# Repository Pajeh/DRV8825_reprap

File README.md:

# DRV8825_reprap
DRV8825 Stepper Schematic based on reprap from Pololu

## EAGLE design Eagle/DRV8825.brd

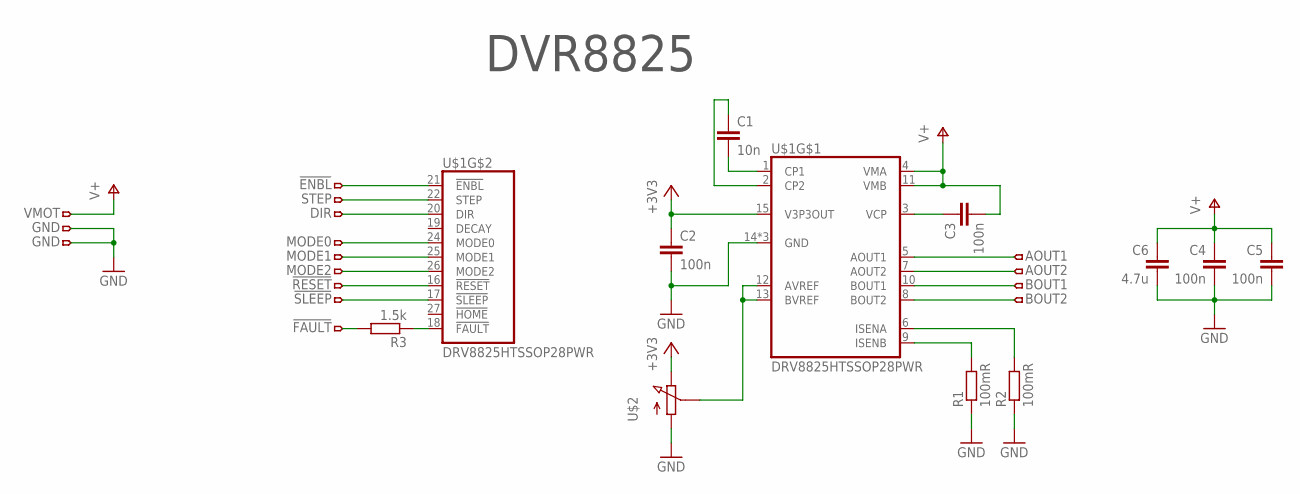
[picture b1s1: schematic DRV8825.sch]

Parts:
C1: 10n; C0603
C2, C3, C4, C5: 100n; C0603
C6: 4.7u; C0603
JP3: AOUT1; 1X01
JP4: AOUT2; 1X01
JP5: BOUT1; 1X01
JP6: BOUT2; 1X01
JP7: !ENBL; 1X01
JP8: STEP; 1X01
JP9: DIR; 1X01
JP10: VMOT; 1X01
JP11: MODE0; 1X01
JP12: MODE1; 1X01
JP13: MODE2; 1X01
JP14: !RESET; 1X01
JP15: !SLEEP; 1X01
JP16, JP18: GND; 1X01
JP17: !FAULT; 1X01
R1, R2: 100mR; R0603
R3: 1.5k; R0603
U$1: DRV8825HTSSOP28PWR; HTSSOP28PWP
U$2: POT-PVZ3A; PVZ3A

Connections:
+3V3: C2.1, U$1.15 (V3P3OUT), U$2.P$3 (E)
GND: C2.2, C4.2, C5.2, C6.2, JP16.1, JP18.1, R1.1, R2.1, U$1.14 (GND), U$1.28 (GND), U$1.EXP (GND), U$2.P$1 (A)
unnamed: C1.2, U$1.1 (CP1)
unnamed: C1.1, U$1.2 (CP2)
unnamed: R3.1, U$1.18 (!FAULT)
unnamed: U$1.12 (AVREF), U$1.13 (BVREF), U$2.P$2 (S)
unnamed: C3.1, U$1.3 (VCP)
unnamed: R1.2, U$1.9 (ISENB)
unnamed: R2.2, U$1.6 (ISENA)
unnamed: JP3.1, U$1.5 (AOUT1)
unnamed: JP4.1, U$1.7 (AOUT2)
unnamed: JP5.1, U$1.10 (BOUT1)
unnamed: JP6.1, U$1.8 (BOUT2)
unnamed: JP7.1, U$1.21 (!ENBL)
unnamed: JP8.1, U$1.22 (STEP)
unnamed: JP9.1, U$1.20 (DIR)
unnamed: JP11.1, U$1.24 (MODE0)
unnamed: JP12.1, U$1.25 (MODE1)
unnamed: JP13.1, U$1.26 (MODE2)
unnamed: JP14.1, U$1.16 (!RESET)
unnamed: JP15.1, U$1.17 (!SLEEP)
unnamed: JP17.1, R3.2
V+: C3.2, C4.1, C5.1, C6.1, JP10.1, U$1.4 (VMA), U$1.11 (VMB)

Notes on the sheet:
DVR8825

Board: 2 copper layers, 27 parts (0 on the bottom side), 23 nets, no tracks yet.
